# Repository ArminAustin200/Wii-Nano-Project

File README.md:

Official Home of the Wii-Nano Project

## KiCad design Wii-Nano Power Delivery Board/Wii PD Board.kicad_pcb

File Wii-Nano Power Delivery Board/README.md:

# Wii-Nano PD Board
Features:
- Designed around the [IP2721](https://github.com/ArminAustin200/Wii-Nano-Project/files/14289473/IP2721.PDF) IC
- USB Type C input
- 15V DC Output (Over USB Power Delivery Standard)
- USB 2.0 data transfer
- Rated for 15V 3A

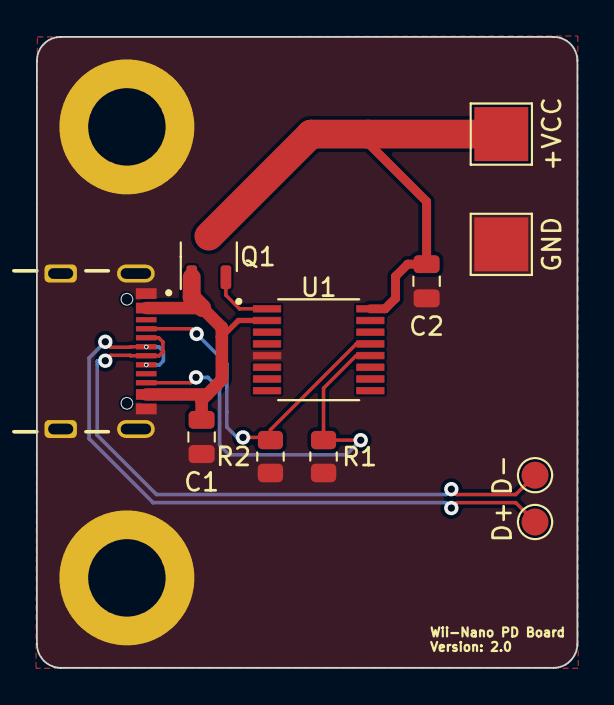
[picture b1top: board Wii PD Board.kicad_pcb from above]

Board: 2 copper layers, 30.0 x 35.1 mm, 11 parts (0 on the bottom side), 8 nets.

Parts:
+VCC: TestPoint_Pad_3.0x3.0mm
C1: 1uF; C_0805_2012Metric
C2: 10uF; C_0805_2012Metric
D+: D-; TestPoint_Pad_D1.5mm
D-: D+; TestPoint_Pad_D1.5mm
GND: TestPoint_Pad_3.0x3.0mm
J1: USB4105-GF-A; GCT_USB4105-GF-A
Q1: DMG3406L; SOT-23-3
R1, R2: 5.11k; R_0805_2012Metric
U1: IP2721; SOP65P640X110-16N

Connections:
+15VOUT: +VCC.1, C2.1, Q1.3 (S), U1.16 (VBUS)
/D+: D+.1, J1.A6 (D+1), J1.B6 (D+2)
/D-: D-.1, J1.A7 (D-1), J1.B7 (D-2)
GNDREF: C1.2, C2.2, GND.1, J1.A1_B12 (GND), J1.B1_A12 (GND), J1.SH1 (SHELL_GND), J1.SH2 (SHELL_GND__1), J1.SH3 (SHELL_GND__2), J1.SH4 (SHELL_GND__3), R1.2, R2.2, U1.5 (GND)
unnamed: J1.A5 (CC1), R2.1, U1.13 (CC1)
unnamed: J1.B5 (CC2), R1.1, U1.12 (CC2)
unnamed: Q1.2 (G), U1.1 (VBUSG)
VBUS: C1.1, J1.A4_B9 (VBUS), J1.B4_A9 (VBUS), Q1.1 (D), U1.2 (VIN)

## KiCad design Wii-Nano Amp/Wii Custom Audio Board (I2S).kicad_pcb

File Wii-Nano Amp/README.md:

# Wii-Nano Amp
Features:
- Designed around the [LM49450](https://www.ti.com/lit/ds/symlink/lm49450.pdf?ts=1707939079954&ref_url=https%253A%252F%252Fwww.ti.com%252Fproduct%252FLM49450) IC
- I2S Audio input direct from Wii motherboard
- I2C Volume control
- Built-in headphone jack
- Headphone presence detection
- 2.5W audio output per (speaker) channel

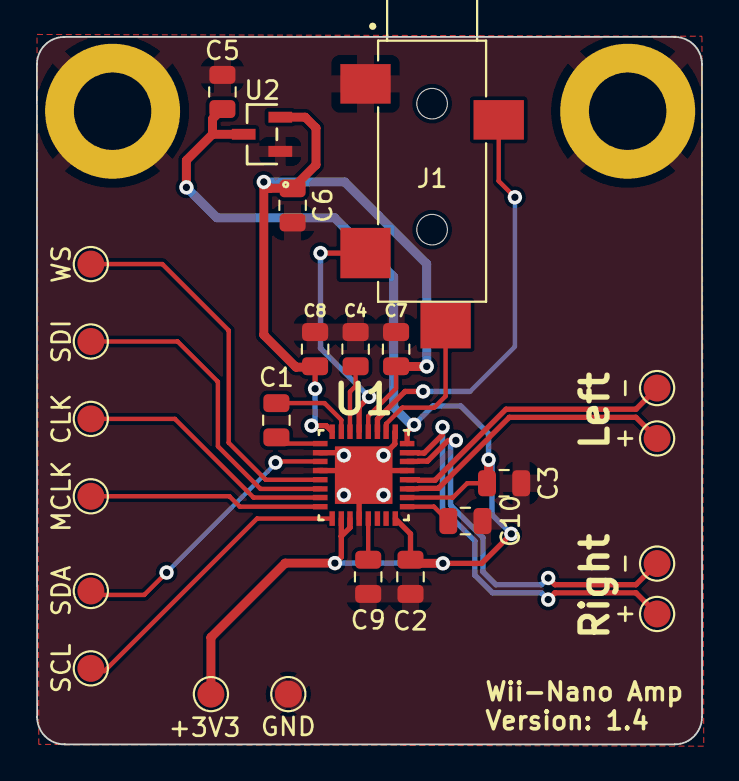
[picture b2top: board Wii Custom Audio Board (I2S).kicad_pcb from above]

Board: 2 copper layers, 37.0 x 39.3 mm, 25 parts (0 on the bottom side), 21 nets.

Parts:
+: Left Speaker; TestPoint_Pad_D1.5mm
+3V3: SCL; TestPoint_Pad_D1.5mm
+#2: Left Speaker; TestPoint_Pad_D1.5mm
-: Left Speaker; TestPoint_Pad_D1.5mm
-#2: Left Speaker; TestPoint_Pad_D1.5mm
C1, C2, C3, C4, C7, C8, C10: 2.2uF; C_0805_2012Metric
C5, C6: 1.0uF; C_0805_2012Metric
C9: 10uF; C_0805_2012Metric
CLK: TestPoint_Pad_D1.5mm
GND: SCL; TestPoint_Pad_D1.5mm
J1: SJ-3524-SMT; CUI_SJ-3524-SMT
MCLK: TestPoint_Pad_D1.5mm
SCL: SCL; TestPoint_Pad_D1.5mm
SDA: SDA; TestPoint_Pad_D1.5mm
SDI: TestPoint_Pad_D1.5mm
U1: LM49450SQ; QFN50P500X500X80-33N
U2: MCP1700T-2502E/TT; SOT-23_MC_MCH
WS: TestPoint_Pad_D1.5mm

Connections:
+3.3V: +3V3.1, C2.1, C3.1, C5.2, U1.10 (DVDD), U1.11 (IOVDD), U1.16 (VDD), U1.18 (LSVDD), U1.24 (LSVDD_2), U2.3 (VIN)
/Left +: +.1, U1.19 (LLS+)
/Left -: -.1, U1.20 (LLS-)
/Right +: +#2.1, U1.23 (RLS+)
/Right -: -#2.1, U1.22 (RLS-)
/Vout: C6.1, C7.2, C8.2, U1.28 (HPVDD), U1.32 (CPVDD), U2.2 (VOUT)
GNDREF: C2.2, C3.2, C4.2, C5.1, C6.2, C7.1, C8.1, C9.2, C10.2, GND.1, J1.1, U1.2 (CPGND), U1.4 (DGND), U1.12 (GND_2), U1.21 (LSGND), U1.25 (HPGND), U1.33 (GND), U2.1 (GND)
unnamed: C10.1, U1.17 (BYPASS)
unnamed: C1.1, U1.31 (C1N)
unnamed: C1.2, U1.1 (C1P)
unnamed: J1.2, U1.29 (HPL)
unnamed: J1.3, U1.27 (HPR)
unnamed: J1.4, U1.26 (HPS)
unnamed: C4.1, U1.30 (HPVSS)
unnamed: CLK.1, U1.7 (I2S_CLK)
unnamed: SDI.1, U1.6 (I2S_SDI)
unnamed: U1.5 (I2S_WS), WS.1
unnamed: MCLK.1, U1.8 (MCLK)
unnamed: C9.1, U1.13 (REF)
unnamed: SCL.1, U1.9 (SCL)
unnamed: SDA.1, U1.3 (SDA)

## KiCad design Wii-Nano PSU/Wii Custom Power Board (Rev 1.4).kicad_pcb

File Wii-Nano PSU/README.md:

# Wii-Nano PSU
Features: 
- Designed around the [TPS564201DDCR](https://www.ti.com/lit/ds/symlink/tps564201.pdf?HQS=dis-dk-null-digikeymode-dsf-pf-null-wwe&ts=1701724916653&ref_url=https%253A%252F%252Fwww.ti.com%252Fgeneral%252Fdocs%252Fsuppproductinfo.tsp%253FdistId%253D10%2526gotoUrl%253Dhttps%253A%252F%252Fwww.ti.com%252Flit%252Fgpn%252Ftps564201) IC
- 4.5-17V input
- 1.0V, 1.15V, and 3.3V output rail for trimmed Wii motherboard
- Enable pin for easy power on/off
- 4.0A current capability per rail

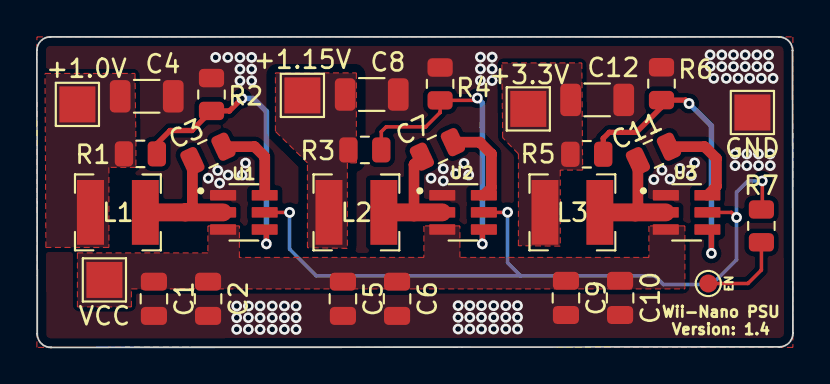
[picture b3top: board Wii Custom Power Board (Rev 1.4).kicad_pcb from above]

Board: 2 copper layers, 42.0 x 17.2 mm, 31 parts (0 on the bottom side), 16 nets.

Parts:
+1.0V, +1.15V, +3.3V: TestPoint_Pad_2.0x2.0mm
C1, C3, C5, C7, C9, C11: 100nF; C_0805_2012Metric
C2, C6, C10: 10uF; C_0805_2012Metric
C4, C8, C12: C_1206_3216Metric
EN: TestPoint_Pad_D1.0mm
GND: TestPoint_Pad_2.0x2.0mm
L1, L2, L3: 2.2uH; L_Bourns-SRN4018
R1: 3.16k; R_0805_2012Metric
R2, R4, R6: 10k; R_0805_2012Metric
R3: 5.11k; R_0805_2012Metric
R5: 33.2k; R_0805_2012Metric
R7: R_0805_2012Metric
U1, U2, U3: TPS564201DDCR; SOT95P280X110-6N
VCC: TestPoint_Pad_2.0x2.0mm

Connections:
1.0V_Out: +1.0V.1, C4.1, L1.2, R1.1
1.15V_Out: +1.15V.1, C8.1, L2.2, R3.1
3.3V_Out: +3.3V.1, C12.1, L3.2, R5.1
+VDC: C1.1, C2.1, C5.1, C6.1, C9.1, C10.1, U1.3 (VIN), U2.3 (VIN), U3.3 (VIN), VCC.1
/Enable: R7.2, U1.5 (EN), U2.5 (EN), U3.5 (EN)
EN_Pad: EN.1, R7.1
GNDREF: C1.2, C2.2, C4.2, C5.2, C6.2, C8.2, C9.2, C10.2, C12.2, GND.1, R2.2, R4.2, R6.2, U1.1 (GND), U2.1 (GND), U3.1 (GND)
unnamed: C3.2, L1.1, U1.2 (SW)
unnamed: C3.1, U1.6 (VBST)
unnamed: R1.2, R2.1, U1.4 (VFB)
unnamed: C7.2, L2.1, U2.2 (SW)
unnamed: C7.1, U2.6 (VBST)
unnamed: R3.2, R4.1, U2.4 (VFB)
unnamed: C11.2, L3.1, U3.2 (SW)
unnamed: C11.1, U3.6 (VBST)
unnamed: R5.2, R6.1, U3.4 (VFB)

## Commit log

2023-12-04 Create Wii-Nano Amp
2023-12-18 Create Gerber
